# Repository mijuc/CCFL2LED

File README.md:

# CCFL2LED

Hi! I'm working on the R&D side of the Поново project. Through our initiative, where we upcycle old electronic devices in exchange for tree seedlings, we’ve noticed that LCD monitors are among the most common items ending up in landfills — and in our repair center as well.

Interestingly, the majority of these monitors share the same issue: the backlight. Most of them use CCFL (cold cathode fluorescent lamp) backlighting, which is often partially or completely non-functional.

As project volunteers, we concluded that replacing the CCFL lamps is not cost-effective. Instead, we aim to modernize these monitors by upgrading them to LED backlighting.

If there are any PCB design or engineering experts among you who would like to provide feedback on the design and concept — we would really appreciate it! We’d also be grateful if you could support our project by sharing it on social media or donating via [OpenCollective](https://opencollective.com/ponovo).

# Why is this change so important?

CCFL lamps are extremely harmful to the environment if broken, as they contain mercury, various metals, and plastics. They also have a significantly shorter lifespan and consume more power compared to LED technology (power consumption can be reduced by up to 40%). Controlling CCFLs requires complex electronics to drive an inverter that can generate up to 2kV AC. These circuits can degrade over time, leading to various failures, such as capacitor damage or degradation, which further impacts device operation.

Additionally, over time, CCFLs tend to yellow, giving the display a reddish or pinkish tint. That’s where LED strips come in — they are very easy to use, safer, more reliable, more available, cheaper, and longer-lasting.

# What are the results after the replacement?

The results were truly unexpected. We didn’t anticipate such a significant improvement in image quality — the colors became much more vibrant. There are no dark areas, and the light is evenly distributed across the screen. Efficiency increased, and power consumption was reduced by 30%.

# Plan and idea
The plan is to create an open-source, universal modular board for displays (composed of multiple parts/modules). This board currently combines several modules. For now, this is sufficient for us to recycle and upgrade monitors that arrive for recycling through the project [Поново](https://www.linkedin.com/company/ponovo/).

Here are picture of the working prototype (with the same chip tested on a 19", 22" and 24" display):

# About the Board

**Warning: This particular board has not yet been fully tested! It has only been tested using separate modules.**
 * **Power supply:** USB-C PD 12V or 12V 3A barrel jack (center-positive)
 * **LED driver:** PT4115 with parallel current sense resistors, calculated based on the [datasheet](https://www.lcsc.com/datasheet/lcsc_datasheet_1810121830_PowTech-CR-PowTech-Shanghai-PT4115B89E_C84512.pdf)
 * **Buck converter:** AP62201 ([datasheet](https://www.lcsc.com/datasheet/lcsc_datasheet_2308101545_Diodes-Incorporated-AP62201WU-7_C3194236.pdf))
 * **USB Type-C PD controller:** CH224K ([datasheet](https://www.laskakit.cz/user/related_files/ch224ds1.pdf))

# Choosing an LED strip

We recommend using a strip with 120 LEDs per meter. It’s also possible to implement the mod with a 60 LEDs/m strip, but the brightness will be noticeably lower. LED's must be 6500k color. Testing of different sizes of LED strip is in progress...
# Power Supply

A maximum of 36W is required (typically around 30W depending on screen size and number of LEDs). There are two input options, selectable via a switch. The USB-C Power Delivery input uses the CH224K chip configured for a 12V output, so it's crucial to ensure that your adapter supports 12V PD — otherwise, it will not work. The second input is a standard DC jack (5.5mm outer, 2.0mm inner, center-positive) with a 12V power supply.

# LED Driver

One PT4115 driver is used per side (especially important for larger screen sizes). Below is a table showing LED strip power consumption.  
Also included is a table with required resistor values. 
# Buck Converter

There are two options for the buck converter:
* Use a prebuilt LM2596 module and connect it to the board.
* Use the integrated circuit on the board — the AP62201WU-7 chip, which provides 5V for the logic board.
The maximum output power required is up to 8W at 5V.

# Modification
  **Warning: Before starting, make sure to clean the workspace and put on gloves!!!**
  
The steps we will go through in this process are:
* Carefully open the display and separate the backlight and the panel from the electronic boards.
* Continue opening the display and separate the panel from the housing, placing it in a clean area (be extremely careful during this step).
* Remove the diffusers, being careful not to mix up their order.
* Replace the CCFL (cold cathode fluorescent lamps), remove them, measure the appropriate length of LED strips, solder 30-40 cm of wire to them, and install them in place of the CCFL, then test them.
* Reinstall the diffusers and test the LED strips again to check if the diffusers have been properly returned to their place.
* Reinstall the panel (check that it is completely clean) and close that part of the display.
* Connect the LED backlight to the power supply board and link it to the display logic board.
* Test the monitor to check if all functions are working on the On-Screen Display (OSD) menu.
* Close the display and put it into operation.
- - - - 
1. **Carefully open the display and separate the backlight and the panel from the electronic boards.**

   -Be careful with the LVDS cable going to the panel

2. **Continue opening the display and separate the panel from the housing, placing it in a clean area (be extremely careful during this step).**

3. **Remove the diffusers, being careful not to mix up their order.**

4. **Replace the CCFL (cold cathode fluorescent lamps), remove them, measure the appropriate length of LED strips, solder 30-40 cm of wire to them, and install them in place of the CCFL, then test them.**

 -An example of bad backlighting

5. **Reinstall the diffusers and test the LED strips again to check if the diffusers have been properly returned to their place.**

  -Badly returned diffusers will have lines on the edges which is the case here

6. **Reinstall the panel (check that it is completely clean) and close that part of the display.**

7. **Connect the LED backlight to the power supply board and link it to the logic board of the display.**

-In this picture, the LED strips are not connected (I don't have a picture when they are connected)

8. **Test the monitor to check if all functions are working on the On-Screen Display (OSD) menu.**

9. **Close the display and put it into operation.**

# Next Steps
  * AC/DC Converter (230V AC to 12V DC)
  * Open-source universal logic board for monitors
# Contact
* Matrix - [@vladanm](https://matrix.to/#/@vladanm:matrix.org)
* LinkedIn - [Vladan Mijuc](https://www.linkedin.com/in/vladan-mijuc-bab922198/)
* Mail - mijuc.edu@gmail.com

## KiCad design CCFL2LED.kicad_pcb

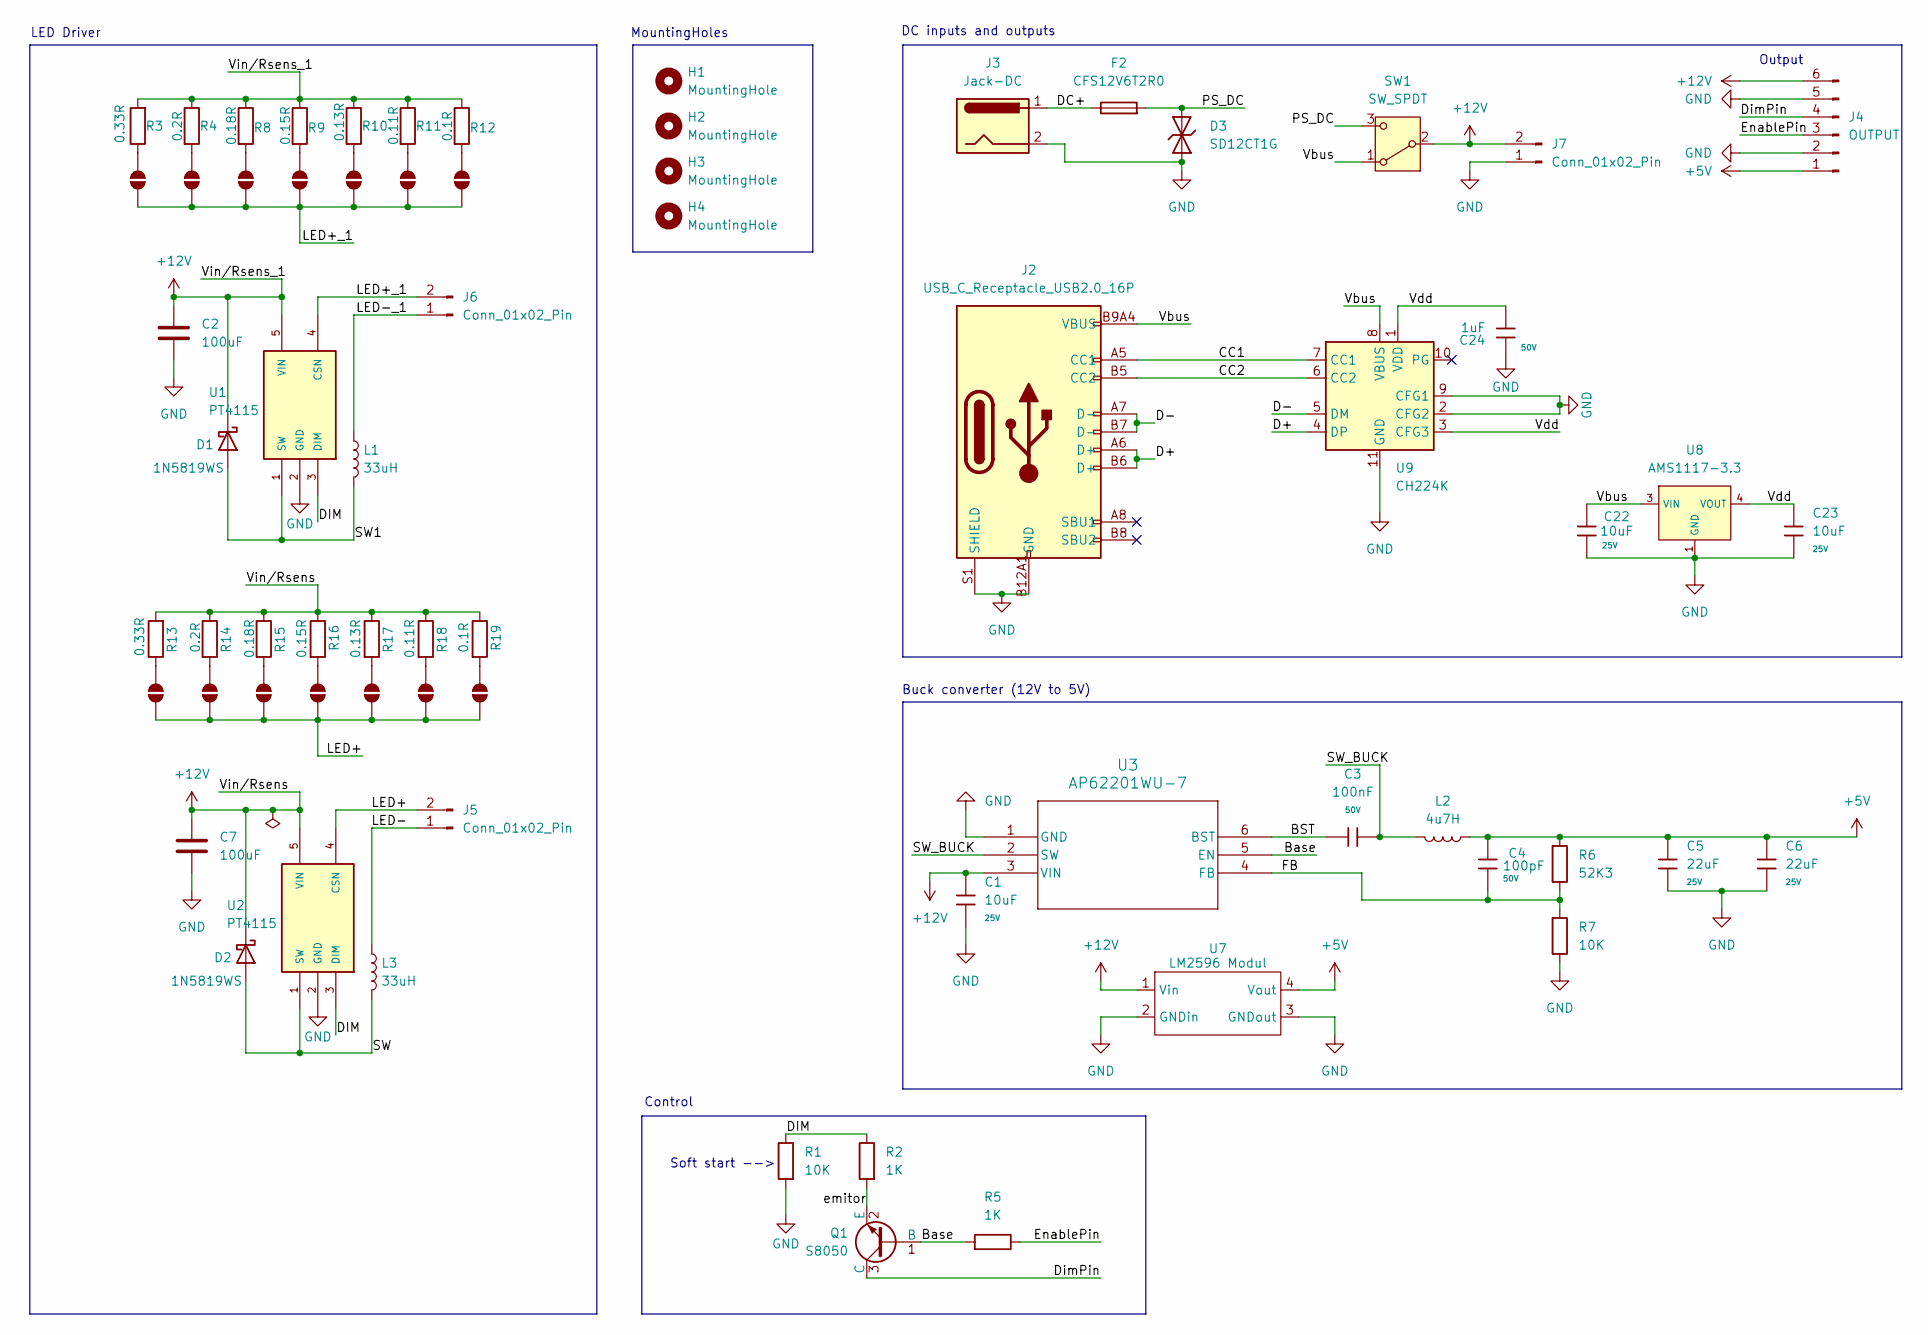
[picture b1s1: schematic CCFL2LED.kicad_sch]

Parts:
C1: 10uF; C_0603; Voltage Rated 25V; Tolerance ±20%; Part CL10A106MA8NRNC; LCSC Part # C1713
C2, C7: 100uF; C_Elec_6.3x7.7; LCSC Part # C7432790
C3: 100nF; C_0603; Voltage Rated 50V; Tolerance ±10%; Part CC0603KRX7R9BB104; LCSC Part # C66501
C4: 100pF; C_0603; Voltage Rated 50V; Tolerance ±5%; Part CL10C101JB8NNNC; LCSC Part # C519407
C5, C6: 22uF; C_0805; Voltage Rated 25V; Tolerance ±20%; Part CL21A226MAQNNNE; LCSC Part # C98190
C22: 10uF; C_0603; Voltage Rated 25V; Tolerance ±20%; Part CL10A106MA8NRNC; LCSC C96446
C23: 10uF; C_0603; Voltage Rated 25V; Tolerance ±20%; Part CL10A106MA8NRNC; LCSC Part # C96446
C24: 1uF; C_0603; Voltage Rated 50V; Tolerance ±10%; Part CL10A105KB8NNNC; LCSC C15849
D1, D2: 1N5819WS; D_SOD-323; LCSC Part # C2828425
D3: SD12CT1G; D_SOD-123FL; Part SMF13CA; LCSC Part # C2985489
F2: CFS12V6T2R0; Fuse_1206_3216Metric; LCSC Part # C163132
H1, H2, H3, H4: MountingHole; MountingHole_2.2mm_M2
J2: USB_C_Receptacle_USB2.0_16P; TYPE-C-SMD_HX-TYPE-C-16PIN; LCSC C2927039
J3: Jack-DC; BarrelJack_Horizontal; LCSC Part # C720557
J4: OUTPUT; PinHeader_1x06_P2.54mm_Vertical
J5, J6, J7: Conn_01x02_Pin; PinSocket_1x02_P2.54mm_Vertical
JP1, JP2, JP3, JP4, JP5, JP6, JP7, JP8, JP9, JP10, JP11, JP12, JP13, JP14: SolderJumper_2_Open; SolderJumper-2_P1.3mm_Open_RoundedPad1.0x1.5mm
L1, L3: 33uH; L_7.3x7.3_H4.5; LCSC Part # C5189937
L2: 4u7H; L_7.3x7.3_H4.5; LCSC Part # C5189748
Q1: S8050; Q_SOT-23; Part S8050; LCSC Part # C18221467
R1, R7: 10K; R_0603; Overload Voltage (Max) 75V; Tolerance ±1%; Part 0603WAF1002T5E; LCSC Part # C25804
R2, R5: 1K; R_0603; Overload Voltage (Max) 75V; Tolerance ±1%; Part 0603WAF1001T5E; LCSC Part # C22548
R3, R13: 0.33R; R_1206_3216Metric_Pad1.30x1.75mm_HandSolder; LCSC C341598
R4, R14: 0.2R; R_1206_3216Metric_Pad1.30x1.75mm_HandSolder; LCSC C160920
R6: 52K3; R_0603; Overload Voltage (Max) 75V; Tolerance ±1%; Part 0603WAF5102T5E; LCSC Part # C2933235
R8, R15: 0.18R; R_1206_3216Metric_Pad1.30x1.75mm_HandSolder; LCSC C912784
R9, R16: 0.15R; R_1206_3216Metric_Pad1.30x1.75mm_HandSolder; LCSC C2991747
R10, R17: 0.13R; R_1206_3216Metric_Pad1.30x1.75mm_HandSolder; LCSC C2683382
R11, R18: 0.11R; R_1206_3216Metric_Pad1.30x1.75mm_HandSolder; LCSC C82532
R12, R19: 0.1R; R_1206_3216Metric_Pad1.30x1.75mm_HandSolder; LCSC C188071
SW1: SW_SPDT; SS-12D11-G7; LCSC C17179526
U1, U2: PT4115; SOT-89-5; LCSC C347356
U3: AP62201WU-7; TSOT26-WU_DIO; LCSC Part C3194236
U7: LM2596 Modul; YAAJ_DCDC_StepDown_LM2596
U8: AMS1117-3.3; SOT-223-3_L6.5-W3.4-P2.30-LS7.0-BR; Output Voltage 3.3V; Dropout Voltage 1.3V@(800mA); Part AMS1117-3.3; LCSC C6186
U9: CH224K; SSOP-10-1EP_3.9x4.9mm_P1mm_EP2.1x3.3mm; LCSC C970725

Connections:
+5V: C4.1, C5.1, C6.1, J4.1, L2.1, R6.1, U7.4 (Vout)
+12V: C1.2, C2.1, C7.1, D1.1 (K), D2.1 (K), J4.6, J7.2, R3.2, R4.1, R8.1, R9.1, R10.1, R11.1, R12.1, R13.2, R14.1, R15.1, R16.1, R17.1, R18.1, R19.1, SW1.2 (B), U1.5 (VIN), U2.5 (VIN), U3.3 (VIN), U7.1 (Vin)
/BST: C3.1, U3.6 (BST)
/Base: Q1.1 (B), R5.1, U3.5 (EN)
/CC1: J2.A5 (CC1), U9.7 (CC1)
/CC2: J2.B5 (CC2), U9.6 (CC2)
/D+: J2.A6 (D+), J2.B6 (D+), U9.4 (DP)
/D-: J2.A7 (D-), J2.B7 (D-), U9.5 (DM)
/DC+: F2.1, J3.1
/DIM: R1.2, R2.2, U1.3 (DIM), U2.3 (DIM)
/DimPin: J4.4, Q1.3 (C)
/EnablePin: J4.3, R5.2
/FB: C4.2, R6.2, R7.1, U3.4 (FB)
/LED+: J5.2, JP8.1 (A), JP9.1 (A), JP10.1 (A), JP11.1 (A), JP12.1 (A), JP13.1 (A), JP14.1 (A), U2.4 (CSN); also elsewhere on the board
/LED+_1: J6.2, JP1.1 (A), JP2.1 (A), JP3.1 (A), JP4.1 (A), JP5.1 (A), JP6.1 (A), JP7.1 (A), U1.4 (CSN); also elsewhere on the board
/LED-: J5.1, L3.1; also elsewhere on the board
/LED-_1: J6.1, L1.1; also elsewhere on the board
/PS_DC: D3.1, F2.2, SW1.3 (C)
/SW: D2.2 (A), L3.2, U2.1 (SW)
/SW1: D1.2 (A), L1.2, U1.1 (SW)
/SW_BUCK: C3.2, L2.2, U3.2 (SW)
/Vbus: C22.1, J2.A9B4 (VBUS), J2.B9A4 (VBUS), SW1.1 (A), U8.3 (VIN), U9.8 (VBUS)
/Vdd: C23.1, C24.1, U8.2 (VOUT), U8.4 (VOUT), U9.1 (VDD), U9.3 (CFG3)
/emitor: Q1.2 (E), R2.1
GND: C1.1, C2.2, C5.2, C6.2, C7.2, C22.2, C23.2, C24.2, D3.2, J2.A12B1 (GND), J2.B12A1 (GND), J2.S1 (SHIELD), J3.2, J4.2, J4.5, J7.1, R1.1, R7.2, U1.2 (GND), U2.2 (GND), U3.1 (GND), U7.2 (GNDin), U7.3 (GNDout), U8.1 (GND), U9.2 (CFG2), U9.9 (CFG1), U9.11 (GND)
unnamed: JP1.2 (B), R3.1
unnamed: JP2.2 (B), R4.2
unnamed: JP3.2 (B), R8.2
unnamed: JP4.2 (B), R9.2
unnamed: JP5.2 (B), R10.2
unnamed: JP6.2 (B), R11.2
unnamed: JP7.2 (B), R12.2
unnamed: JP8.2 (B), R13.1
unnamed: JP9.2 (B), R14.2
unnamed: JP10.2 (B), R15.2
unnamed: JP11.2 (B), R16.2
unnamed: JP12.2 (B), R17.2
unnamed: JP13.2 (B), R18.2
unnamed: JP14.2 (B), R19.2

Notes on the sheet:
Buck converter (12V to 5V)
LED Driver
Control
Soft start -->
MountingHoles
Output
DC inputs and outputs

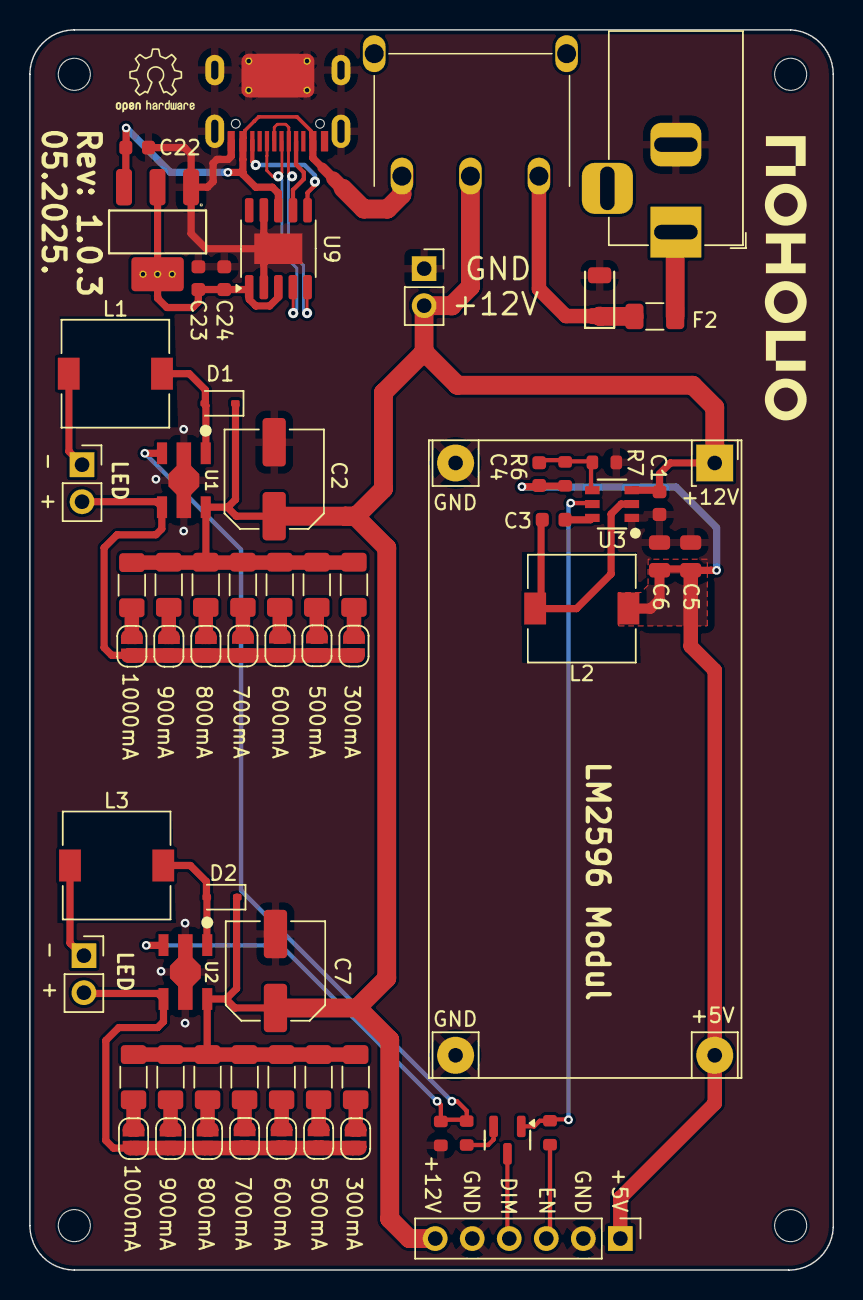
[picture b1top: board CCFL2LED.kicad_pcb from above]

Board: 2 copper layers, 55.1 x 85.1 mm, 68 parts (0 on the bottom side), 39 nets.

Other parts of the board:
+  -: Conn_01x02_Pin; PinSocket_1x02_P2.54mm_Vertical
+  -#2: Conn_01x02_Pin; PinSocket_1x02_P2.54mm_Vertical

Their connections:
/LED+: + -#2.2; also elsewhere on the board
/LED+_1: + -.2; also elsewhere on the board
/LED-: + -#2.1; also elsewhere on the board
/LED-_1: + -.1; also elsewhere on the board

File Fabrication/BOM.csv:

"Reference","Qty","Value","Footprint","LCSC Part #","LCSC"
"C1","1","10uF","PCM_JLCPCB:C_0603","C1713","C96446"
"C2,C7","2","100uF","Capacitor_SMD:C_Elec_6.3x7.7","C7432790","C7432790"
"C3","1","100nF","PCM_JLCPCB:C_0603","C66501","C14663"
"C4","1","100pF","PCM_JLCPCB:C_0603","C519407","C14858"
"C5,C6","2","22uF","PCM_JLCPCB:C_0805","C98190","C45783"
"C22,C23","2","10uF","PCM_JLCPCB:C_0603","C96446","C96446"
"C24","1","1uF","PCM_JLCPCB:C_0603","C15849","C15849"
"D1,D2","2","1N5819WS","Diode_SMD:D_SOD-323","C2828425","C2828425"
"D3","1","SD12CT1G","PCM_JLCPCB:D_SOD-123FL","C2985489","C19077508"
"F2","1","CFS12V6T2R0","Fuse:Fuse_1206_3216Metric","C163132","C163132"
"J2","1","USB_C_Receptacle_USB2.0_16P","PCM_JLCPCB:TYPE-C-SMD_HX-TYPE-C-16PIN","C2927039","C2927039"
"J3","1","Jack-DC","Connector_BarrelJack:BarrelJack_Horizontal","C3010534","C3010534"
"J5,J6,J7","3","Conn_01x02_Pin","Connector_PinSocket_2.54mm:PinSocket_1x02_P2.54mm_Vertical","",""
"L1,L3","2","33uH","Inductor_SMD:L_7.3x7.3_H4.5","C5189937","C5189937"
"L2","1","4u7H","Inductor_SMD:L_7.3x7.3_H4.5","C5189748","C5189748"
"Q1","1","S8050","PCM_JLCPCB:Q_SOT-23","C18221467","C364312"
"R1,R7","2","10K","PCM_JLCPCB:R_0603","C25804","C25804"
"R2,R5","2","1K","PCM_JLCPCB:R_0603","C22548","C21190"
"R3,R13","2","0.33R","Resistor_SMD:R_1206_3216Metric_Pad1.30x1.75mm_HandSolder","C341598","C341598"
"R4,R14","2","0.2R","Resistor_SMD:R_1206_3216Metric_Pad1.30x1.75mm_HandSolder","C160920","C160920"
"R6","1","52K3","PCM_JLCPCB:R_0603","C2933235","C23196"
"R8,R15","2","0.18R","Resistor_SMD:R_1206_3216Metric_Pad1.30x1.75mm_HandSolder","C912784","C912784"
"R9,R16","2","0.15R","Resistor_SMD:R_1206_3216Metric_Pad1.30x1.75mm_HandSolder","C2991747","C2991747"
"R10,R17","2","0.13R","Resistor_SMD:R_1206_3216Metric_Pad1.30x1.75mm_HandSolder","C2683382","C2683382"
"R11,R18","2","0.11R","Resistor_SMD:R_1206_3216Metric_Pad1.30x1.75mm_HandSolder","C82532","C82532"
"R12,R19","2","0.1R","Resistor_SMD:R_1206_3216Metric_Pad1.30x1.75mm_HandSolder","C188071","C188071"
"SW1","1","SW_SPDT","CustomSwitchFootprint:SS-12D11-G7","C17179526","C17179526"
"U1,U2","2","PT4115","LED_Driver_Global:SOT-89-5","C347356","C347356"
"U3","1","AP62201WU-7","Buck_Converters_Global:TSOT26-WU_DIO","C3194236","C3194236"
"U7","1","LM2596 Modul","Buck_Converters_Global:YAAJ_DCDC_StepDown_LM2596","",""
"U8","1","AMS1117-3.3","PCM_JLCPCB:SOT-223-3_L6.5-W3.4-P2.30-LS7.0-BR","C6186","C6186"
"U9","1","CH224K","Package_SO:SSOP-10-1EP_3.9x4.9mm_P1mm_EP2.1x3.3mm","C970725","C970725"

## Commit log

2025-05-13 1.0.3 Version files
2025-05-19 Update schematic and pictures
2025-05-24 Trace update
    - Update pictures
    - Update kicad_pcb
    - Update fabrication files
